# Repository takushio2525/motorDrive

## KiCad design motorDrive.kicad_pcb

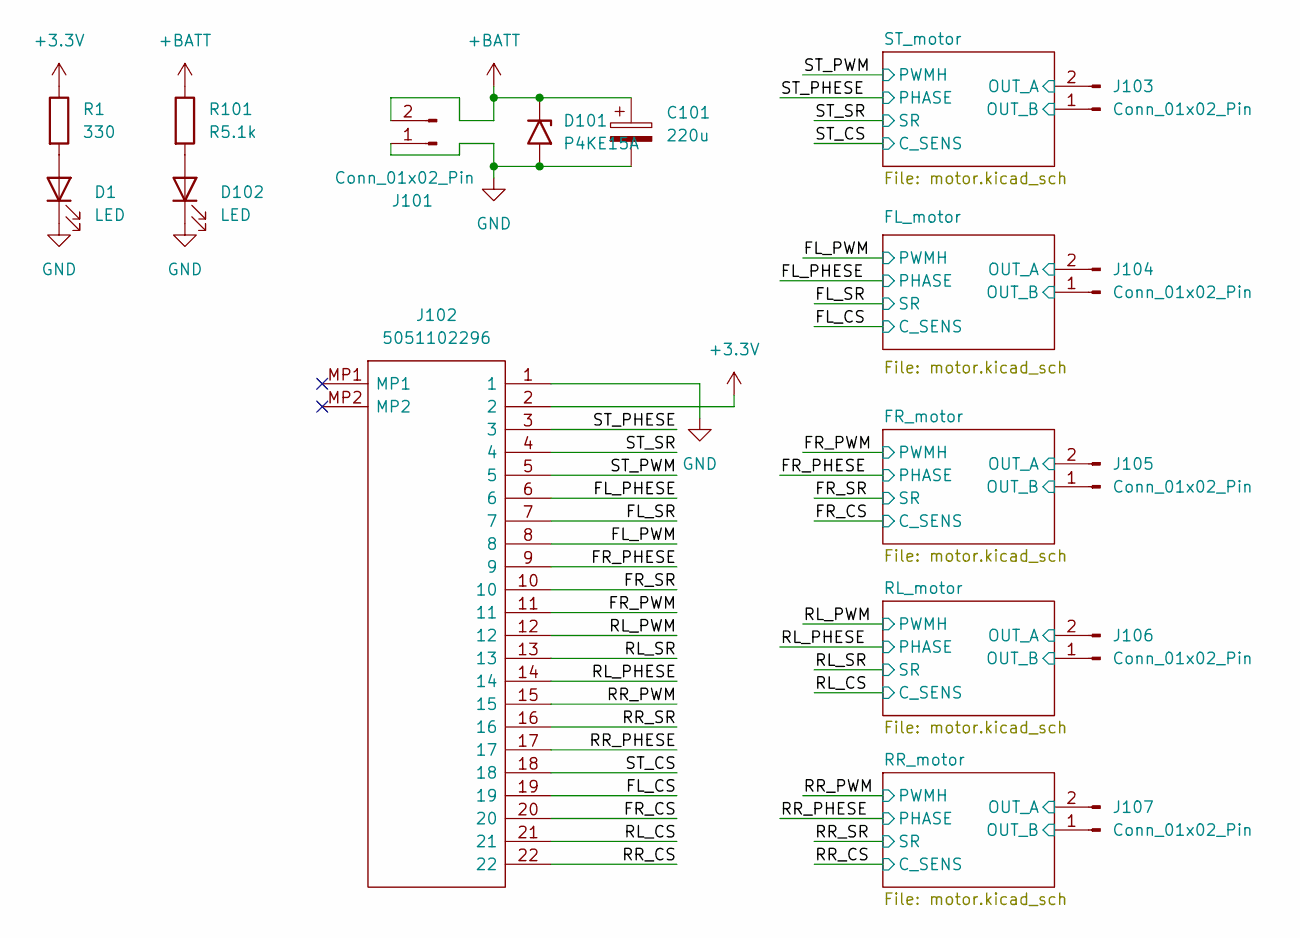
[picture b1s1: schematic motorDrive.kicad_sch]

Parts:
C101: 220u; CP_Elec_6.3x5.9
D1, D102: LED; LED_0603_1608Metric
D101: P4KE15A; D_A-405_P10.16mm_Horizontal
J101: Conn_01x02_Pin; AMASS_XT30U-M_1x02_P5.0mm_Vertical
J102: 5051102296; Manufacturer_Part_Number 5051102296
J103, J104, J105, J106, J107: Conn_01x02_Pin; AMASS_XT30U-M_MOTOR
R1: 330; R_0603_1608Metric
R101: R5.1k; R_0603_1608Metric

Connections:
+3.3V: J102.2, R1.1; also elsewhere on the board
+BATT: C101.1, D101.1 (A1), J101.2, R101.1; also elsewhere on the board
/FL_CS: J102.19; also elsewhere on the board
/FL_PHESE: J102.6; also elsewhere on the board
/FL_PWM: J102.8; also elsewhere on the board
/FL_SR: J102.7; also elsewhere on the board
/FL_motor/OUT_A: J104.2; also elsewhere on the board
/FL_motor/SB: J104.1; also elsewhere on the board
/FR_CS: J102.20; also elsewhere on the board
/FR_PHESE: J102.9; also elsewhere on the board
/FR_PWM: J102.11; also elsewhere on the board
/FR_SR: J102.10; also elsewhere on the board
/FR_motor/OUT_A: J105.2; also elsewhere on the board
/FR_motor/SB: J105.1; also elsewhere on the board
/RL_CS: J102.21; also elsewhere on the board
/RL_PHESE: J102.14; also elsewhere on the board
/RL_PWM: J102.12; also elsewhere on the board
/RL_SR: J102.13; also elsewhere on the board
/RL_motor/OUT_A: J106.2; also elsewhere on the board
/RL_motor/SB: J106.1; also elsewhere on the board
/RR_CS: J102.22; also elsewhere on the board
/RR_PHESE: J102.17; also elsewhere on the board
/RR_PWM: J102.15; also elsewhere on the board
/RR_SR: J102.16; also elsewhere on the board
/RR_motor/OUT_A: J107.2; also elsewhere on the board
/RR_motor/SB: J107.1; also elsewhere on the board
/ST_CS: J102.18; also elsewhere on the board
/ST_PHESE: J102.3; also elsewhere on the board
/ST_PWM: J102.5; also elsewhere on the board
/ST_SR: J102.4; also elsewhere on the board
/ST_motor/OUT_A: J103.2; also elsewhere on the board
/ST_motor/SB: J103.1; also elsewhere on the board
GND: C101.2, D1.1 (K), D101.2 (A2), D102.1 (K), J101.1, J102.1; also elsewhere on the board
unnamed: D1.2 (A), R1.2
unnamed: D102.2 (A), R101.2

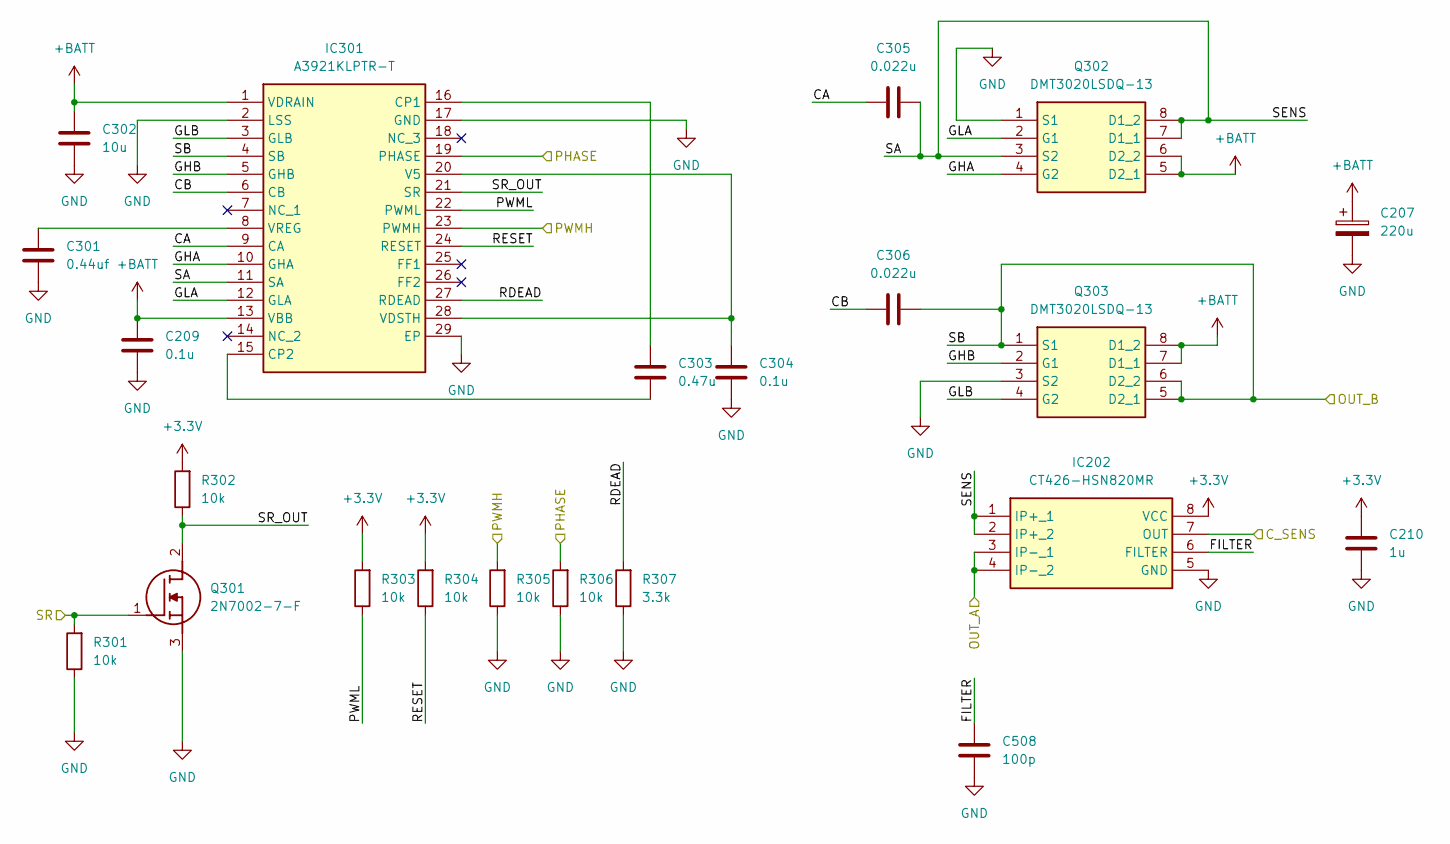
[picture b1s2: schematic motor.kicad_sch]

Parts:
C207: 220u; CP_Elec_6.3x5.9
C209, C304: 0.1u; C_0603_1608Metric
C210: 1u; C_0603_1608Metric
C301: 0.44uf; C_0603_1608Metric
C302: 10u; C_0603_1608Metric
C303: 0.47u; C_0603_1608Metric
C305, C306: 0.022u; C_0603_1608Metric
C508: 100p; C_0603_1608Metric
IC202: CT426-HSN820MR; SOIC127P600X172-8N; Manufacturer_Part_Number CT426-HSN820MR
IC301: A3921KLPTR-T; A3944KLPTRT; Manufacturer_Part_Number A3921KLPTR-T; Mouser Part Number 250-A3921KLPTR-T
Q301: 2N7002-7-F; SOT95P240X100-3N; Manufacturer_Part_Number 2N7002-7-F
Q302, Q303: DMT3020LSDQ-13; SOIC127P600X170-8N; Manufacturer_Part_Number DMT3020LSDQ-13; Mouser Part Number 621-DMT3020LSDQ-13
R301, R302, R303, R304, R305, R306: 10k; R_0603_1608Metric
R307: 3.3k; R_0603_1608Metric

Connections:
+3.3V: C210.1, IC202.8 (VCC), R302.2, R303.2, R304.2; also elsewhere on the board
+BATT: C207.1, C209.1, C302.1, IC301.1 (VDRAIN), IC301.13 (VBB), Q302.5 (D2_1), Q302.6 (D2_2), Q303.7 (D1_1), Q303.8 (D1_2); also elsewhere on the board
/FL_PHESE: IC301.19 (PHASE), R306.2; also elsewhere on the board
/FL_PWM: IC301.23 (PWMH), R305.2; also elsewhere on the board
/FL_SR: Q301.1 (G), R301.2; also elsewhere on the board
/FL_motor/CA: C305.2, IC301.9 (CA)
/FL_motor/CB: C306.2, IC301.6 (CB)
/FL_motor/GHA: IC301.10 (GHA), Q302.4 (G2)
/FL_motor/GHB: IC301.5 (GHB), Q303.2 (G1)
/FL_motor/GLA: IC301.12 (GLA), Q302.2 (G1)
/FL_motor/GLB: IC301.3 (GLB), Q303.4 (G2)
/FL_motor/PWML: IC301.22 (PWML), R303.1
/FL_motor/RDEAD: IC301.27 (RDEAD), R307.2
/FL_motor/RESET: IC301.24 (RESET), R304.1
/FL_motor/SB: C306.1, IC301.4 (SB), Q303.1 (S1), Q303.5 (D2_1), Q303.6 (D2_2); also elsewhere on the board
/FL_motor/SR_OUT: IC301.21 (SR), Q301.2 (D), R302.1
/ST_CS: IC202.7 (OUT); also elsewhere on the board
/ST_motor/OUT_A: IC202.3 (IP-_1), IC202.4 (IP-_2); also elsewhere on the board
GND: C207.2, C209.2, C210.2, C301.2, C302.2, C304.2, C508.2, IC202.5 (GND), IC301.2 (LSS), IC301.17 (GND), IC301.29 (EP), Q301.3 (S), Q302.1 (S1), Q303.3 (S2), R301.1, R305.1, R306.1, R307.1; also elsewhere on the board
unnamed: C303.1, IC301.16 (CP1)
unnamed: C303.2, IC301.15 (CP2)
unnamed: C304.1, IC301.20 (V5), IC301.28 (VDSTH)
unnamed: C301.1, IC301.8 (VREG)

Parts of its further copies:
C201, C401, C501, C601: 0.44uf; C_0603_1608Metric
C202, C402, C502, C602: 10u; C_0603_1608Metric
C203, C403, C503, C603: 0.47u; C_0603_1608Metric
C204, C309, C404, C409, C504, C509, C604, C609: 0.1u; C_0603_1608Metric
C205, C206, C405, C406, C505, C506, C605, C606: 0.022u; C_0603_1608Metric
C208, C308, C408, C608: 100p; C_0603_1608Metric
C307, C407, C507, C607: 220u; CP_Elec_6.3x5.9
C310, C410, C510, C610: 1u; C_0603_1608Metric
IC201, IC401, IC501, IC601: A3921KLPTR-T; A3944KLPTRT; Manufacturer_Part_Number A3921KLPTR-T; Mouser Part Number 250-A3921KLPTR-T
IC302, IC402, IC502, IC602: CT426-HSN820MR; SOIC127P600X172-8N; Manufacturer_Part_Number CT426-HSN820MR
Q201, Q401, Q501, Q601: 2N7002-7-F; SOT95P240X100-3N; Manufacturer_Part_Number 2N7002-7-F
Q202, Q203, Q402, Q403, Q502, Q503, Q602, Q603: DMT3020LSDQ-13; SOIC127P600X170-8N; Manufacturer_Part_Number DMT3020LSDQ-13; Mouser Part Number 621-DMT3020LSDQ-13
R201, R202, R203, R204, R205, R206, R401, R402, R403, R404, R405, R406, R501, R502, R503, R504, R505, R506, R601, R602, R603, R604, R605, R606: 10k; R_0603_1608Metric
R207, R407, R507, R607: 3.3k; R_0603_1608Metric

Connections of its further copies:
+3.3V: C310.1, C410.1, C510.1, C610.1, IC302.8 (VCC), IC402.8 (VCC), IC502.8 (VCC), IC602.8 (VCC), R202.2, R203.2, R204.2, R402.2, R403.2, R404.2, R502.2, R503.2, R504.2, R602.2, R603.2, R604.2; also elsewhere on the board
+BATT: C202.1, C307.1, C309.1, C402.1, C407.1, C409.1, C502.1, C507.1, C509.1, C602.1, C607.1, C609.1, IC201.1 (VDRAIN), IC201.13 (VBB), IC401.1 (VDRAIN), IC401.13 (VBB), IC501.1 (VDRAIN), IC501.13 (VBB), IC601.1 (VDRAIN), IC601.13 (VBB), Q202.5 (D2_1), Q202.6 (D2_2), Q203.7 (D1_1), Q203.8 (D1_2), Q402.5 (D2_1), Q402.6 (D2_2), Q403.7 (D1_1), Q403.8 (D1_2), Q502.5 (D2_1), Q502.6 (D2_2), Q503.7 (D1_1), Q503.8 (D1_2), Q602.5 (D2_1), Q602.6 (D2_2), Q603.7 (D1_1), Q603.8 (D1_2); also elsewhere on the board
/FL_CS: IC302.7 (OUT); also elsewhere on the board
/FL_motor/FILTER: C308.1, IC302.6 (FILTER)
/FL_motor/OUT_A: IC302.3 (IP-_1), IC302.4 (IP-_2); also elsewhere on the board
/FR_CS: IC402.7 (OUT); also elsewhere on the board
/FR_PHESE: IC401.19 (PHASE), R406.2; also elsewhere on the board
/FR_PWM: IC401.23 (PWMH), R405.2; also elsewhere on the board
/FR_SR: Q401.1 (G), R401.2; also elsewhere on the board
/FR_motor/CA: C405.2, IC401.9 (CA)
/FR_motor/CB: C406.2, IC401.6 (CB)
/FR_motor/FILTER: C408.1, IC402.6 (FILTER)
/FR_motor/GHA: IC401.10 (GHA), Q402.4 (G2)
/FR_motor/GHB: IC401.5 (GHB), Q403.2 (G1)
/FR_motor/GLA: IC401.12 (GLA), Q402.2 (G1)
/FR_motor/GLB: IC401.3 (GLB), Q403.4 (G2)
/FR_motor/OUT_A: IC402.3 (IP-_1), IC402.4 (IP-_2); also elsewhere on the board
/FR_motor/PWML: IC401.22 (PWML), R403.1
/FR_motor/RDEAD: IC401.27 (RDEAD), R407.2
/FR_motor/RESET: IC401.24 (RESET), R404.1
/FR_motor/SA: C405.1, IC401.11 (SA), IC402.1 (IP+_1), IC402.2 (IP+_2), Q402.3 (S2), Q402.7 (D1_1), Q402.8 (D1_2)
/FR_motor/SB: C406.1, IC401.4 (SB), Q403.1 (S1), Q403.5 (D2_1), Q403.6 (D2_2); also elsewhere on the board
/FR_motor/SR_OUT: IC401.21 (SR), Q401.2 (D), R402.1
/RL_CS: IC502.7 (OUT); also elsewhere on the board
/RL_PHESE: IC501.19 (PHASE), R506.2; also elsewhere on the board
/RL_PWM: IC501.23 (PWMH), R505.2; also elsewhere on the board
/RL_SR: Q501.1 (G), R501.2; also elsewhere on the board
/RL_motor/CA: C505.2, IC501.9 (CA)
/RL_motor/CB: C506.2, IC501.6 (CB)
/RL_motor/GHA: IC501.10 (GHA), Q502.4 (G2)
/RL_motor/GHB: IC501.5 (GHB), Q503.2 (G1)
/RL_motor/GLA: IC501.12 (GLA), Q502.2 (G1)
/RL_motor/GLB: IC501.3 (GLB), Q503.4 (G2)
/RL_motor/OUT_A: IC502.3 (IP-_1), IC502.4 (IP-_2); also elsewhere on the board
/RL_motor/PWML: IC501.22 (PWML), R503.1
/RL_motor/RDEAD: IC501.27 (RDEAD), R507.2
/RL_motor/RESET: IC501.24 (RESET), R504.1
/RL_motor/SA: C505.1, IC501.11 (SA), IC502.1 (IP+_1), IC502.2 (IP+_2), Q502.3 (S2), Q502.7 (D1_1), Q502.8 (D1_2)
/RL_motor/SB: C506.1, IC501.4 (SB), Q503.1 (S1), Q503.5 (D2_1), Q503.6 (D2_2); also elsewhere on the board
/RL_motor/SR_OUT: IC501.21 (SR), Q501.2 (D), R502.1
/RR_CS: IC602.7 (OUT); also elsewhere on the board
/RR_PHESE: IC601.19 (PHASE), R606.2; also elsewhere on the board
/RR_PWM: IC601.23 (PWMH), R605.2; also elsewhere on the board
/RR_SR: Q601.1 (G), R601.2; also elsewhere on the board
/RR_motor/CA: C605.2, IC601.9 (CA)
/RR_motor/CB: C606.2, IC601.6 (CB)
/RR_motor/FILTER: C608.1, IC602.6 (FILTER)
/RR_motor/GHA: IC601.10 (GHA), Q602.4 (G2)
/RR_motor/GHB: IC601.5 (GHB), Q603.2 (G1)
/RR_motor/GLA: IC601.12 (GLA), Q602.2 (G1)
/RR_motor/GLB: IC601.3 (GLB), Q603.4 (G2)
/RR_motor/OUT_A: IC602.3 (IP-_1), IC602.4 (IP-_2); also elsewhere on the board
/RR_motor/PWML: IC601.22 (PWML), R603.1
/RR_motor/RDEAD: IC601.27 (RDEAD), R607.2
/RR_motor/RESET: IC601.24 (RESET), R604.1
/RR_motor/SA: C605.1, IC601.11 (SA), IC602.1 (IP+_1), IC602.2 (IP+_2), Q602.3 (S2), Q602.7 (D1_1), Q602.8 (D1_2)
/RR_motor/SB: C606.1, IC601.4 (SB), Q603.1 (S1), Q603.5 (D2_1), Q603.6 (D2_2); also elsewhere on the board
/RR_motor/SR_OUT: IC601.21 (SR), Q601.2 (D), R602.1
/ST_PHESE: IC201.19 (PHASE), R206.2; also elsewhere on the board
/ST_PWM: IC201.23 (PWMH), R205.2; also elsewhere on the board
/ST_SR: Q201.1 (G), R201.2; also elsewhere on the board
/ST_motor/CA: C205.2, IC201.9 (CA)
/ST_motor/CB: C206.2, IC201.6 (CB)
/ST_motor/GHA: IC201.10 (GHA), Q202.4 (G2)
/ST_motor/GHB: IC201.5 (GHB), Q203.2 (G1)
/ST_motor/GLA: IC201.12 (GLA), Q202.2 (G1)
/ST_motor/GLB: IC201.3 (GLB), Q203.4 (G2)
/ST_motor/PWML: IC201.22 (PWML), R203.1
/ST_motor/RDEAD: IC201.27 (RDEAD), R207.2
/ST_motor/RESET: IC201.24 (RESET), R204.1
/ST_motor/SB: C206.1, IC201.4 (SB), Q203.1 (S1), Q203.5 (D2_1), Q203.6 (D2_2); also elsewhere on the board
/ST_motor/SR_OUT: IC201.21 (SR), Q201.2 (D), R202.1
GND: C201.2, C202.2, C204.2, C208.2, C307.2, C308.2, C309.2, C310.2, C401.2, C402.2, C404.2, C407.2, C408.2, C409.2, C410.2, C501.2, C502.2, C504.2, C507.2, C509.2, C510.2, C601.2, C602.2, C604.2, C607.2, C608.2, C609.2, C610.2, IC201.2 (LSS), IC201.17 (GND), IC201.29 (EP), IC302.5 (GND), IC401.2 (LSS), IC401.17 (GND), IC401.29 (EP), IC402.5 (GND), IC501.2 (LSS), IC501.17 (GND), IC501.29 (EP), IC502.5 (GND), IC601.2 (LSS), IC601.17 (GND), IC601.29 (EP), IC602.5 (GND), Q201.3 (S), Q202.1 (S1), Q203.3 (S2), Q401.3 (S), Q402.1 (S1), Q403.3 (S2), Q501.3 (S), Q502.1 (S1), Q503.3 (S2), Q601.3 (S), Q602.1 (S1), Q603.3 (S2), R201.1, R205.1, R206.1, R207.1, R401.1, R405.1, R406.1, R407.1, R501.1, R505.1, R506.1, R507.1, R601.1, R605.1, R606.1, R607.1; also elsewhere on the board
unnamed: C203.1, IC201.16 (CP1)
unnamed: C203.2, IC201.15 (CP2)
unnamed: C204.1, IC201.20 (V5), IC201.28 (VDSTH)
unnamed: C201.1, IC201.8 (VREG)
unnamed: C403.1, IC401.16 (CP1)
unnamed: C403.2, IC401.15 (CP2)
unnamed: C404.1, IC401.20 (V5), IC401.28 (VDSTH)
unnamed: C401.1, IC401.8 (VREG)
unnamed: C503.1, IC501.16 (CP1)
unnamed: C503.2, IC501.15 (CP2)
unnamed: C504.1, IC501.20 (V5), IC501.28 (VDSTH)
unnamed: C501.1, IC501.8 (VREG)
unnamed: C603.1, IC601.16 (CP1)
unnamed: C603.2, IC601.15 (CP2)
unnamed: C604.1, IC601.20 (V5), IC601.28 (VDSTH)
unnamed: C601.1, IC601.8 (VREG)

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
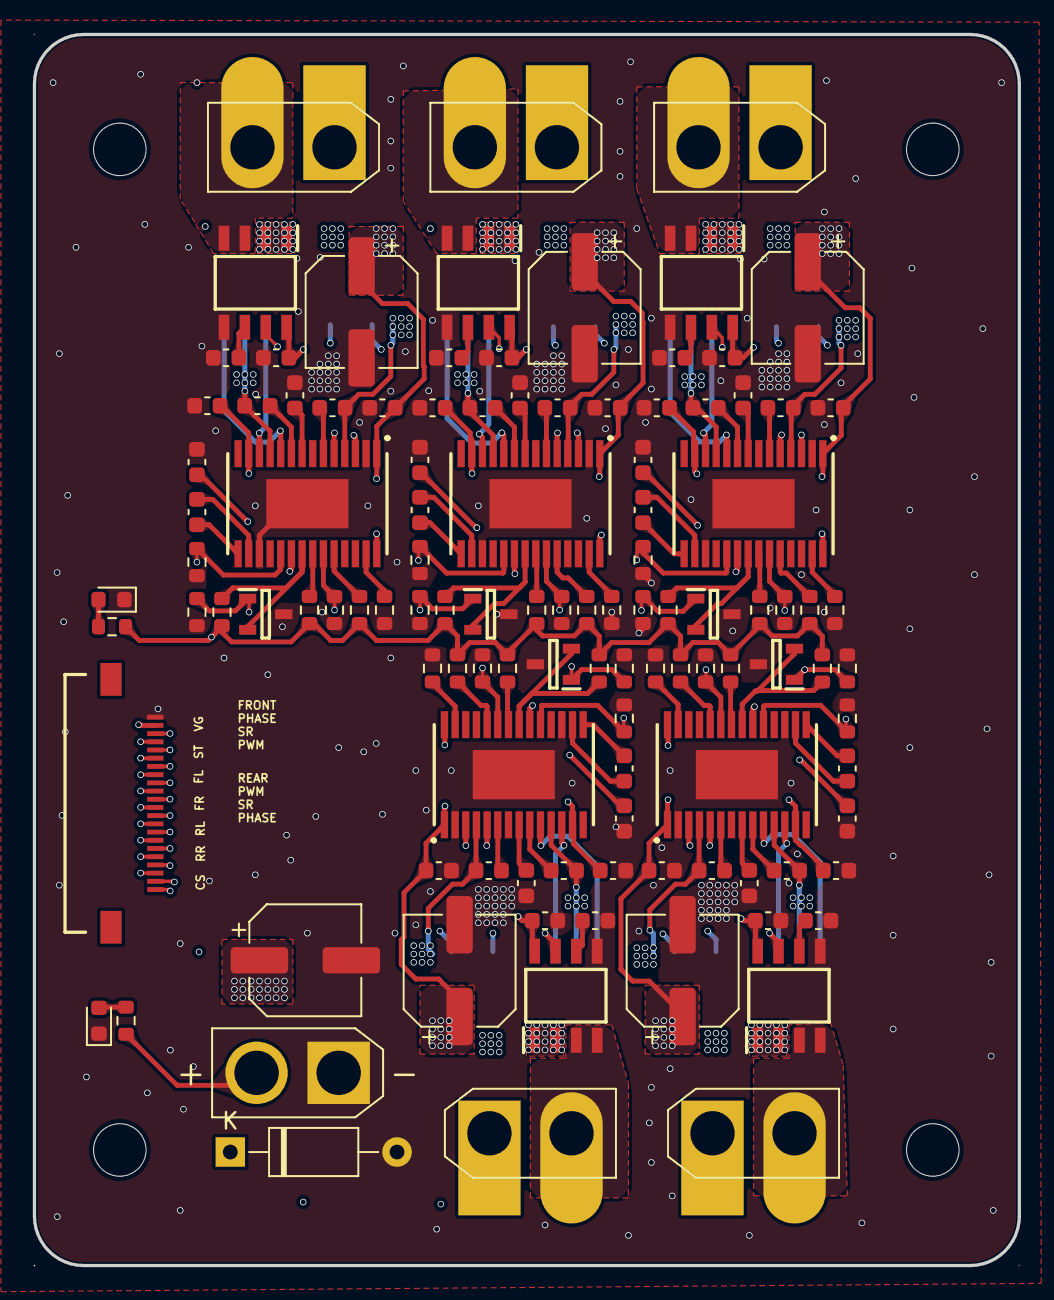
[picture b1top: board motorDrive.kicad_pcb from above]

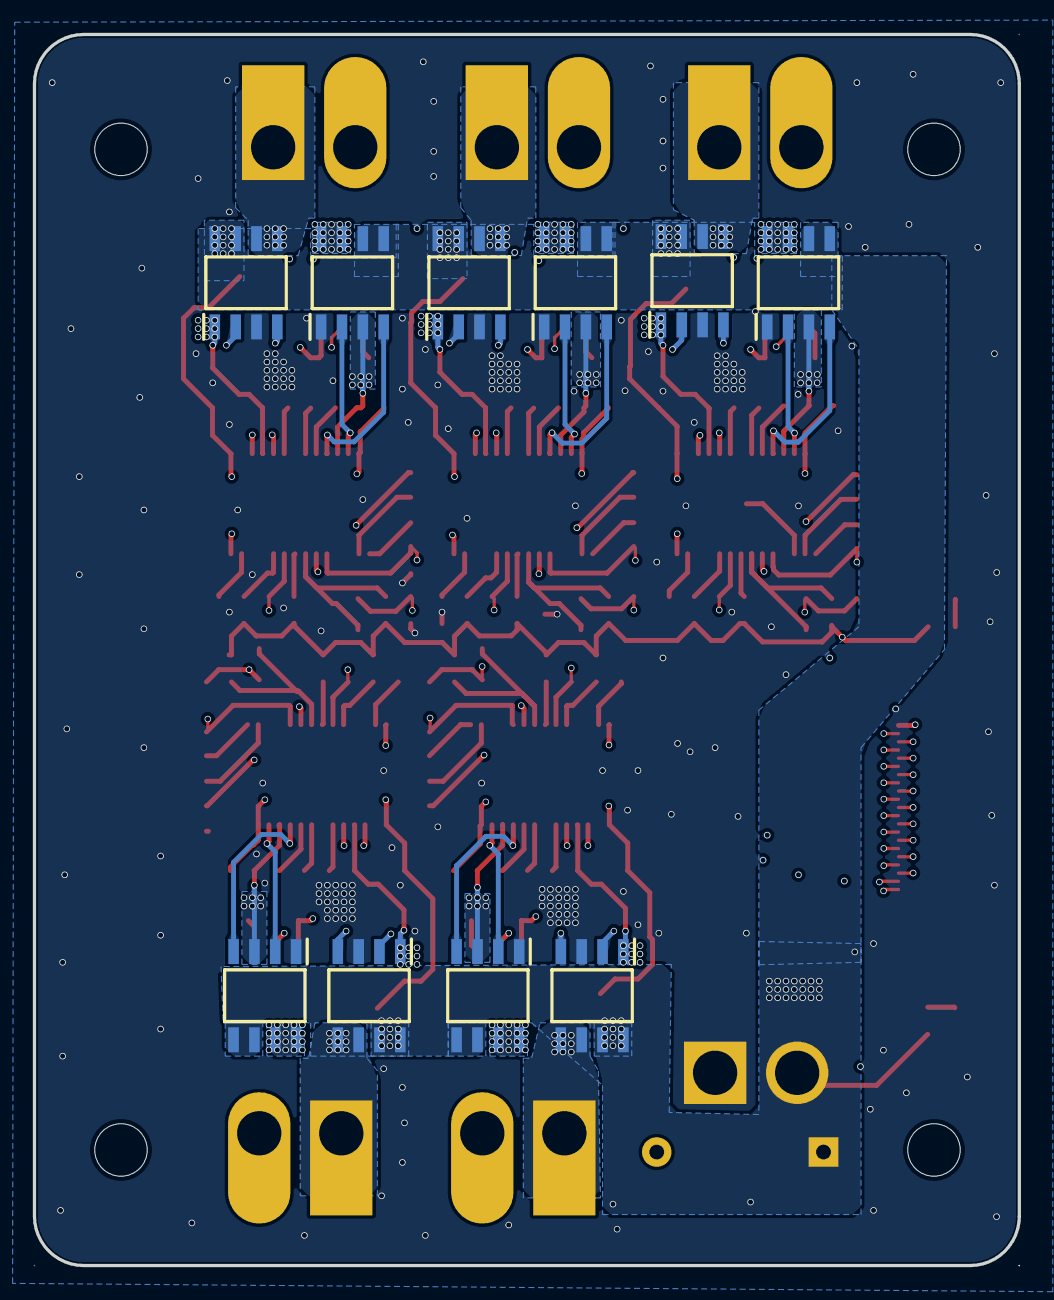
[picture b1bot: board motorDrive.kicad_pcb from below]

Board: 4 copper layers, 60.0 x 75.0 mm, 123 parts (10 on the bottom side), 115 nets.

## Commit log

2025-12-14 アンテナチョンパ
2025-12-14 っっっっっｙ
2025-12-15 ういいいいいいいいいいい
2025-12-18 パラダイス
